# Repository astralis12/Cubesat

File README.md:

# UGMSat-2
A bachelor thesis final project aimed to create CubeSat for students in Indonesia with the approach of model-based system engineering in the field of aerospace

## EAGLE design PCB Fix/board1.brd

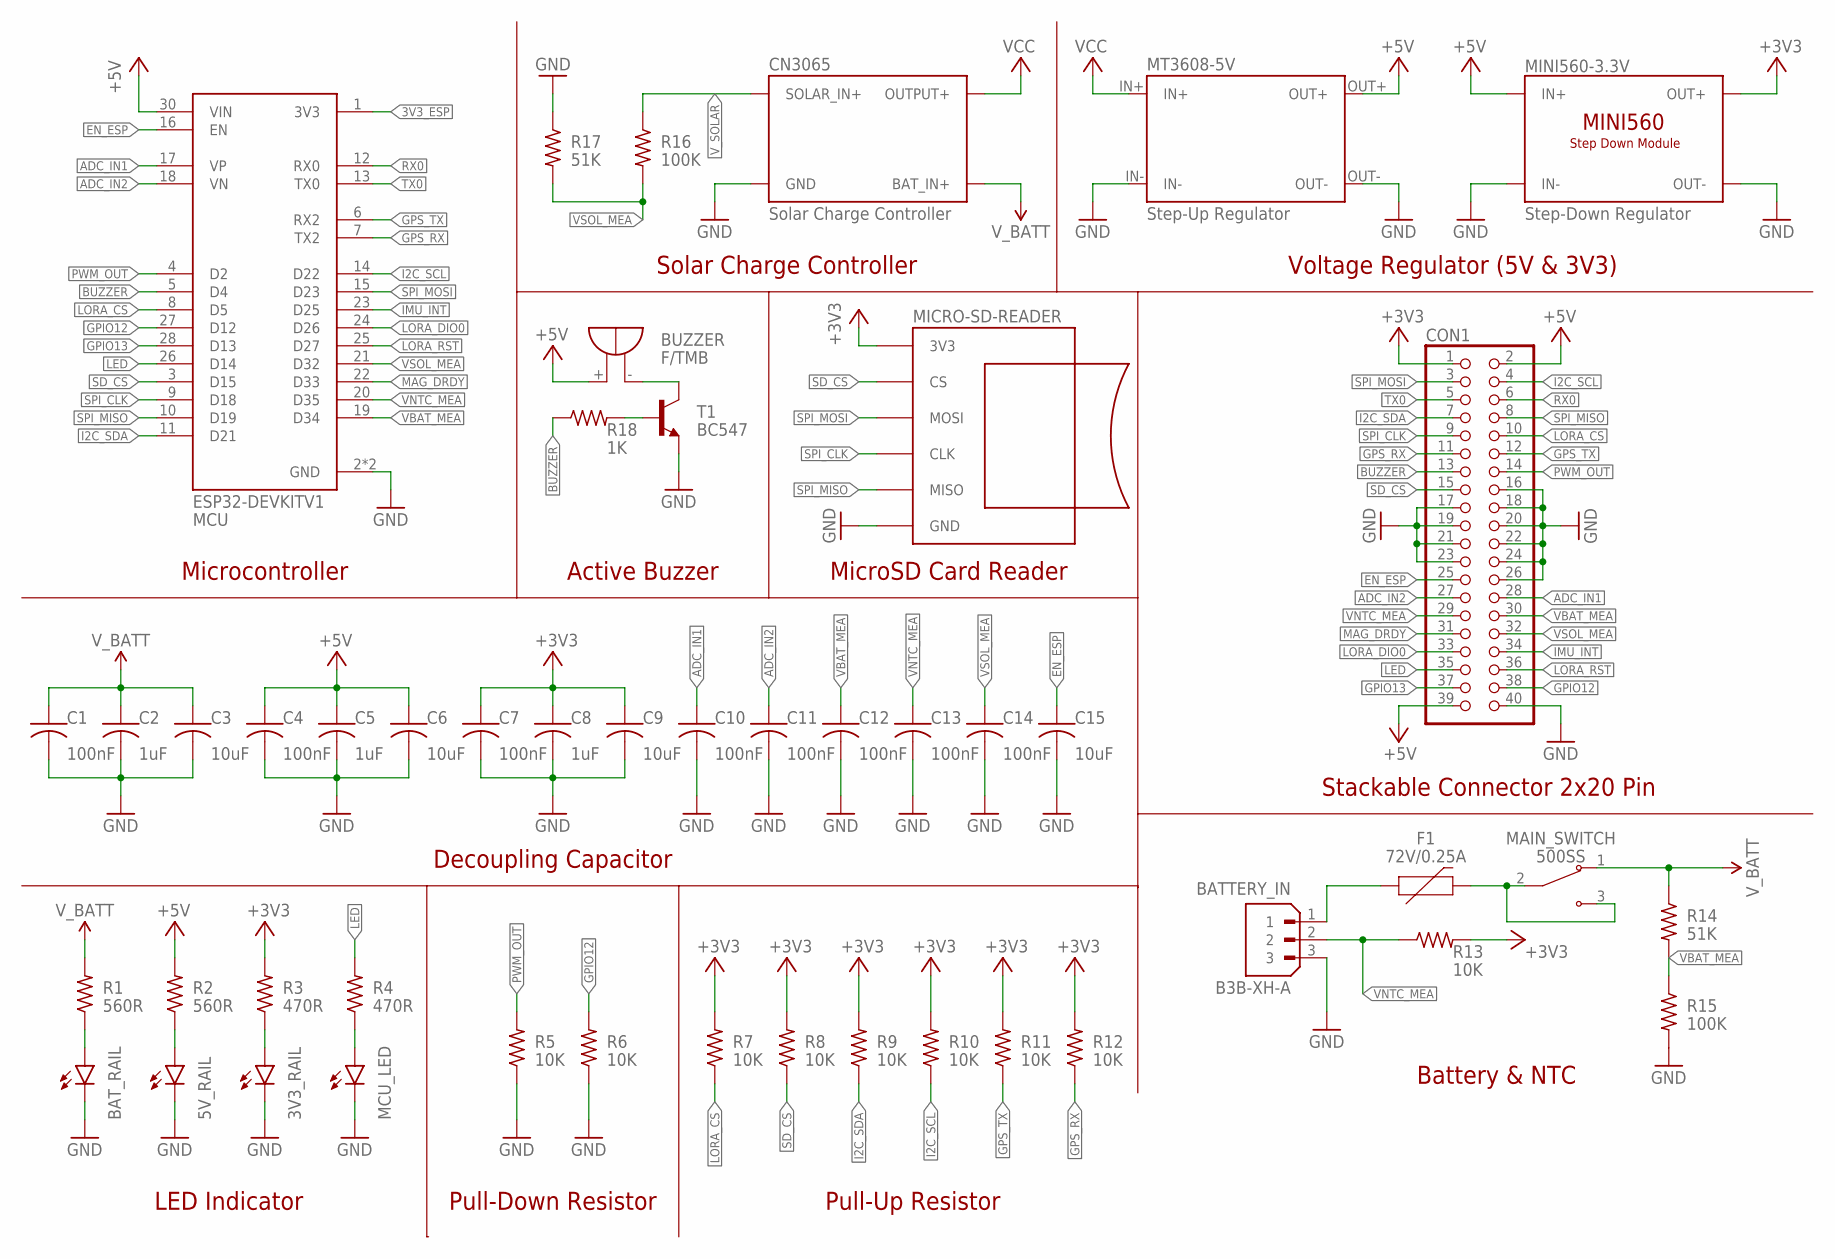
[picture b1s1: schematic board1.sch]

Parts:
3V3_RAIL, 5V_RAIL: LEDCHIP-LED0805; CHIP-LED0805
BATTERY_IN: B3B-XH-A; JST_B3B-XH-A
BAT_RAIL: LEDCHIP-LED0805; CHIP-LED0805
BUZZER: F/TMB
C1, C4, C7, C10, C11, C12, C13, C14: 100nF; C0805
C2, C5, C8: 1uF; C0805
C3, C6, C9, C15: 10uF; C0805
CN3065: Solar Charge Controller; CN3065
CON1: PINHD-2X20; 2X20
ESP32-DEVKITV1: MCU; MODULE_ESP32_DEVKIT_V1
F1: 72V/0.25A; PTH
MAIN_SWITCH: 500SS; SW_500SSP1S1M2REA
MCU_LED: LEDCHIP-LED0805; CHIP-LED0805
MICRO-SD-READER: MICROSD-READERUP-TOP; MICROSD-READER-FACING_UP(TOP_LAYER)
MINI560-3.3V: Step-Down Regulator; MINI560-THT
MT3608-5V: Step-Up Regulator; MT3608
R1, R2: 560R; R0805
R3, R4: 470R; R0805
R5, R6, R7, R8, R9, R10, R11, R12, R13: 10K; R0805
R14, R17: 51K; R0805
R15, R16: 100K; R0805
R18: 1K; R0805
T1: BC547; TO92

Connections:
3V3_ESP: ESP32-DEVKITV1.1 (3V3)
+3V3: C7.1, C8.1, C9.1, CON1.1, MICRO-SD-READER.3V3, MINI560-3.3V.1OUT+ (OUT+), MINI560-3.3V.2OUT+ (OUT+), R3.2, R7.2, R8.2, R9.2, R10.2, R11.2, R12.2, R13.2
+5V: BUZZER.+, C4.1, C5.1, C6.1, CON1.2, CON1.39, ESP32-DEVKITV1.30 (VIN), MINI560-3.3V.1IN+ (IN+), MINI560-3.3V.2IN+ (IN+), MT3608-5V.OUT+, R2.2
ADC_IN1: C10.1, CON1.28, ESP32-DEVKITV1.17 (VP)
ADC_IN2: C11.1, CON1.27, ESP32-DEVKITV1.18 (VN)
BUZZER: CON1.13, ESP32-DEVKITV1.5 (D4), R18.1
EN_ESP: C15.1, CON1.25, ESP32-DEVKITV1.16 (EN)
GND: 3V3_RAIL.C, 5V_RAIL.C, BATTERY_IN.3, BAT_RAIL.C, C1.2, C2.2, C3.2, C4.2, C5.2, C6.2, C7.2, C8.2, C9.2, C10.2, C11.2, C12.2, C13.2, C14.2, C15.2, CN3065.BAT- (GND), CN3065.OUT- (GND), CN3065.SC- (GND), CON1.16, CON1.17, CON1.18, CON1.19, CON1.20, CON1.21, CON1.22, CON1.23, CON1.24, CON1.26, CON1.40, ESP32-DEVKITV1.2 (GND), ESP32-DEVKITV1.29 (GND), MCU_LED.C, MICRO-SD-READER.GND, MINI560-3.3V.1IN- (IN-), MINI560-3.3V.1OUT- (OUT-), MINI560-3.3V.2IN- (IN-), MINI560-3.3V.2OUT- (OUT-), MT3608-5V.IN-, MT3608-5V.OUT-, R5.1, R6.1, R15.2, R17.1, T1.1 (E)
GPIO12: CON1.38, ESP32-DEVKITV1.27 (D12), R6.2
GPIO13: CON1.37, ESP32-DEVKITV1.28 (D13)
GPS_RX: CON1.11, ESP32-DEVKITV1.7 (TX2), R12.1
GPS_TX: CON1.12, ESP32-DEVKITV1.6 (RX2), R11.1
I2C_SCL: CON1.4, ESP32-DEVKITV1.14 (D22), R10.1
I2C_SDA: CON1.7, ESP32-DEVKITV1.11 (D21), R9.1
IMU_INT: CON1.34, ESP32-DEVKITV1.23 (D25)
LED: CON1.35, ESP32-DEVKITV1.26 (D14), R4.2
LORA_CS: CON1.10, ESP32-DEVKITV1.8 (D5), R7.1
LORA_DIO0: CON1.33, ESP32-DEVKITV1.24 (D26)
LORA_RST: CON1.36, ESP32-DEVKITV1.25 (D27)
MAG_DRDY: CON1.31, ESP32-DEVKITV1.22 (D33)
unnamed: BATTERY_IN.1, F1.P$1 (1)
unnamed: BUZZER.-, T1.3 (C)
unnamed: F1.P$2 (2), MAIN_SWITCH.2 (COM), MAIN_SWITCH.3 (NO)
unnamed: R18.2, T1.2 (B)
unnamed: MCU_LED.A, R4.1
unnamed: 3V3_RAIL.A, R3.1
unnamed: BAT_RAIL.A, R1.1
unnamed: 5V_RAIL.A, R2.1
PWM_OUT: CON1.14, ESP32-DEVKITV1.4 (D2), R5.2
RX0: CON1.6, ESP32-DEVKITV1.12 (RX0)
SD_CS: CON1.15, ESP32-DEVKITV1.3 (D15), MICRO-SD-READER.CS, R8.1
SPI_CLK: CON1.9, ESP32-DEVKITV1.9 (D18), MICRO-SD-READER.CLK
SPI_MISO: CON1.8, ESP32-DEVKITV1.10 (D19), MICRO-SD-READER.MISO
SPI_MOSI: CON1.3, ESP32-DEVKITV1.15 (D23), MICRO-SD-READER.MOSI
TX0: CON1.5, ESP32-DEVKITV1.13 (TX0)
VBAT_MEA: C12.1, CON1.30, ESP32-DEVKITV1.19 (D34), R14.2, R15.1
VCC: CN3065.OUT+ (OUTPUT+), MT3608-5V.IN+
VNTC_MEA: BATTERY_IN.2, C13.1, CON1.29, ESP32-DEVKITV1.20 (D35), R13.1
VSOL_MEA: C14.1, CON1.32, ESP32-DEVKITV1.21 (D32), R16.2, R17.2
V_BATT: C1.1, C2.1, C3.1, CN3065.BAT+ (BAT_IN+), MAIN_SWITCH.1 (NC), R1.2, R14.1
V_SOLAR: CN3065.SC+ (SOLAR_IN+), R16.1

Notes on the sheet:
Microcontroller
Decoupling Capacitor
LED Indicator
Pull-Down Resistor
Pull-Up Resistor
Battery & NTC
Active Buzzer
MicroSD Card Reader
Solar Charge Controller
Stackable Connector 2x20 Pin
Voltage Regulator (5V & 3V3)

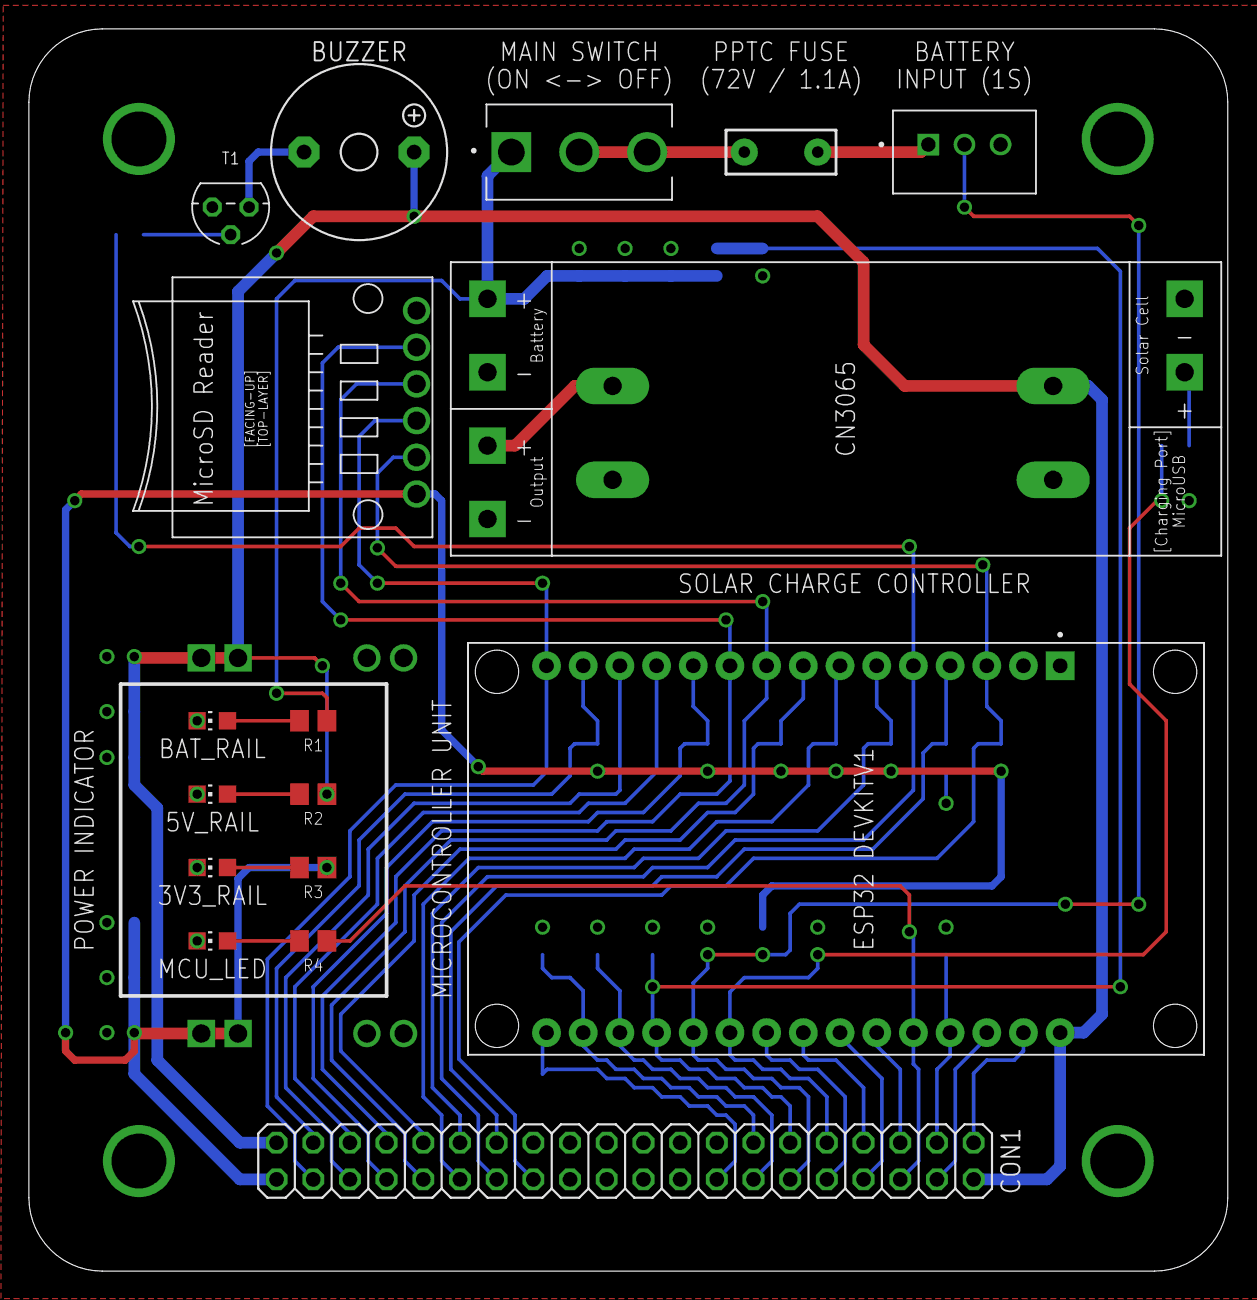
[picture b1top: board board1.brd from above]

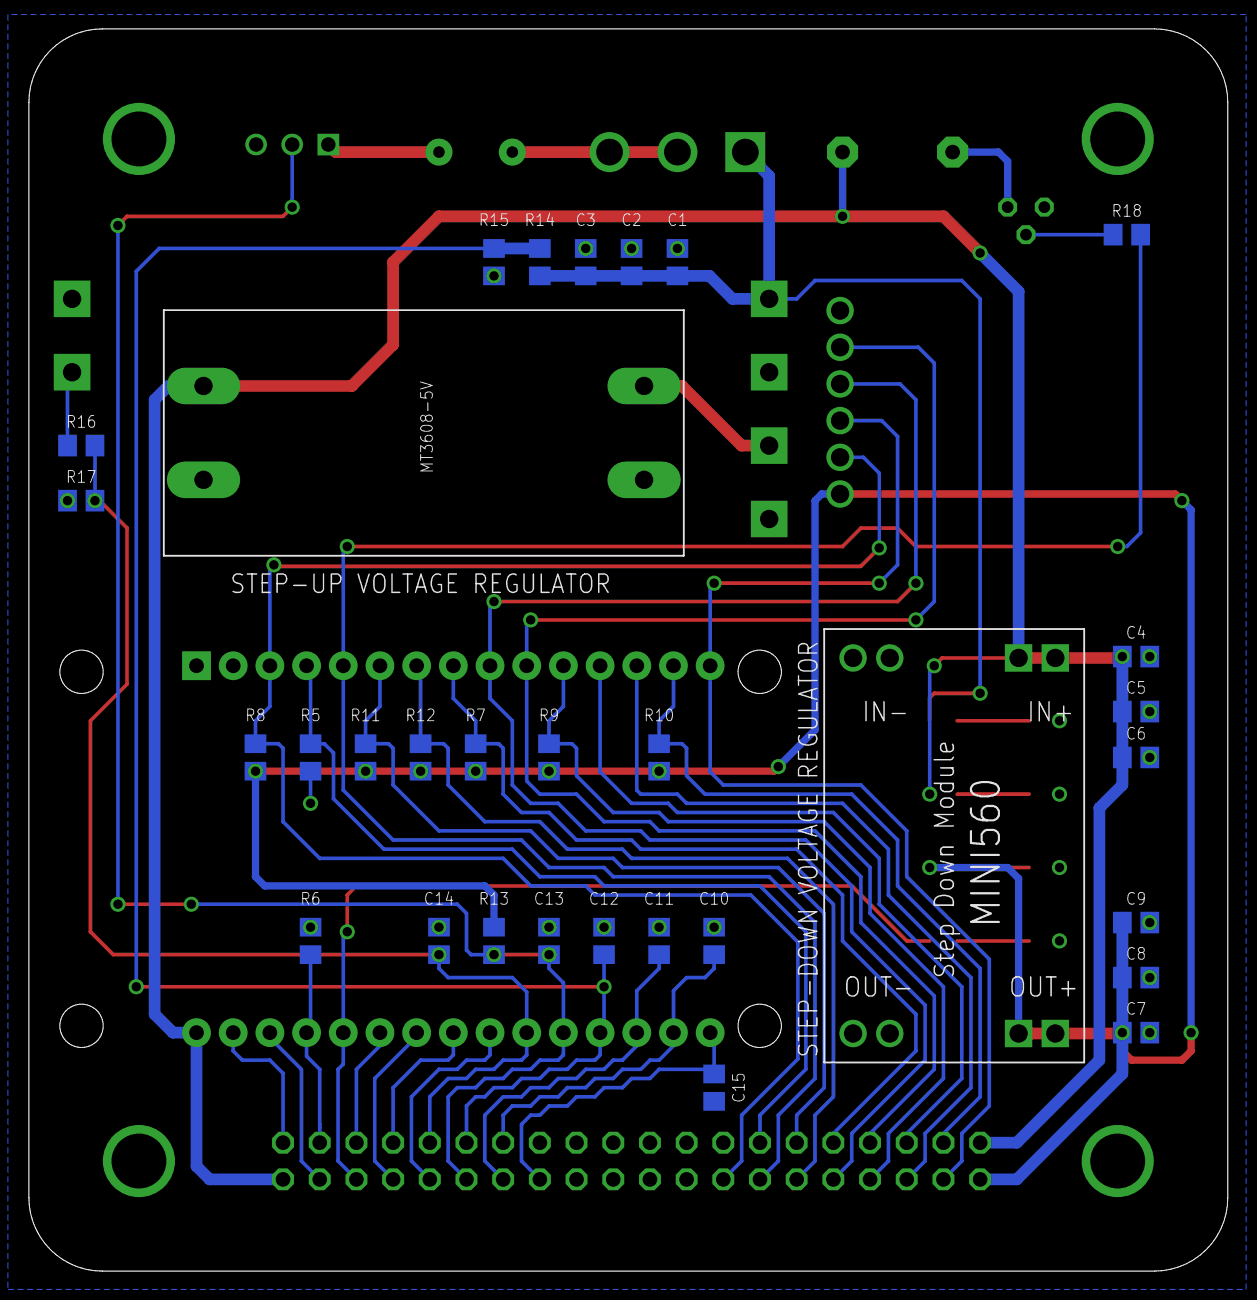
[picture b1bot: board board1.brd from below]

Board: 2 copper layers, 83.0 x 86.0 mm, 48 parts (31 on the bottom side), 40 nets.

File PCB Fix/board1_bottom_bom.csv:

Comment,Designator,Footprint,LCSC Part #
1K,R18,R0805,
1uF,C2 C5 C8,C0805,
10K,R5 R6 R7 R8 R9 R10 R11 R12 R13,R0805,
10uF,C3 C6 C9 C15,C0805,
51K,R14 R17,R0805,
100K,R15 R16,R0805,
100nF,C1 C4 C7 C10 C11 C12 C13 C14,C0805,

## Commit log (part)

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2025-10-12 example for git
2025-10-12 second trial
2025-10-12 0 MBSE backbone v1
2025-11-29 Printed OBC and EPS
    double layer minus the interface documentation

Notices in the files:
parts and their libraries:
SparkFun-Fuses: Licensing: Creative Commons ShareAlike 4.0 International - https://creativecommons.org/licenses/by-sa/4.0
